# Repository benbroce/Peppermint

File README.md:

# Peppermint
Christmas 2018 &amp; Square Inch Challenge (Hackaday)

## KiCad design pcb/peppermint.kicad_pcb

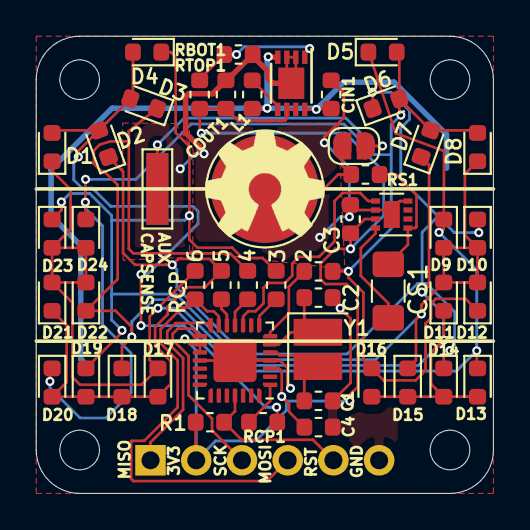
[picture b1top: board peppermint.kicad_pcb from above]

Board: 2 copper layers, 25.4 x 25.4 mm, 55 parts (1 on the bottom side), 27 nets.

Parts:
2, 3, 4, 5, 6: R; R_0603_1608Metric
BT1: CR2032; BatteryHolder_LINX_BAT-HLD-001-SMT_SOLDERPAD
C1, C2: C; C_0603_1608Metric
C3, C4: 0.1uF; C_0603_1608Metric
CIN1: 4.7uF; C_0603_1608Metric
COUT1: 10uF; C_0603_1608Metric
CS1: 22nF; C_1206_3216Metric_Pad1.42x1.75mm_HandSolder
D1, D2, D3, D4, D5, D6, D7, D8, D9, D10, D11, D12, D13, D14, D15, D16, D17, D18, D19, D20, D21, D22, D23, D24: LED; LED_0603_1608Metric
J1: AVR-ISP-6; SIP-6_AVR_ISP
J2: SENSE_ELECTRODE; CapSense_MaskedPad_D6.0mm
J3: SENSE_ELECTRODE_AUX; SMD_WIREPAD_4.0x1.25mm
JP1: Jumper_NO_Small; SolderJumper-2_P1.3mm_Open_RoundedPad1.0x1.5mm
L1: 4.7uH; L_0603_1608Metric
R1: 10K; R_0603_1608Metric
RBOT1: 1M; R_0603_1608Metric
RCP1: R; R_0603_1608Metric
RS1: 10K; R_0603_1608Metric
RTOP1: 1.69M; R_0603_1608Metric
U1: ATmega328P-MMH; QFN-28-1EP_4x4mm_P0.45mm_EP2.4x2.4mm
U2: MCP16251T-I/CH; DFN-8-1EP_3x2mm_P0.5mm_EP1.75x1.45mm
U3: AT42QT1010-MAH; DFN-8-1EP_2x2mm_P0.5mm_EP0.9x1.5mm
Y1: 8MHz; Crystal_SMD_NX3225GD
hole: hole; MountingHole_2.2mm_M2_DIN965
hole#2, hole#3, hole#4: hole; MountingHole_2.2mm_M2_DIN965

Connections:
+3V3: C3.2, C4.2, COUT1.1, J1.2, R1.1, RTOP1.1, U1.3, U1.16, U1.17, U2.6, U2.7, U3.7
CAPSENSE: U1.10, U3.5
CP1: RCP1.2, U1.1
CP2: 2.2, U1.7
CP3: 3.2, U1.8
CP4: 4.2, U1.11
CP5: 5.2, U1.12
CP6: 6.2, J1.4, U1.13
GND: BT1.2, C1.1, C2.2, C3.1, C4.1, CIN1.2, COUT1.2, J1.6, RBOT1.2, U1.4, U1.18, U1.29, U2.2, U2.3, U2.9, U3.4, U3.6, U3.9
MISO: J1.1, U1.14
unnamed: BT1.1, CIN1.1, L1.1, U2.4, U2.8
unnamed: C1.2, U1.5, Y1.2
unnamed: C2.1, U1.6, Y1.1
unnamed: CS1.1, RS1.2, U3.1
unnamed: CS1.2, U3.8
unnamed: 6.1, D1.1, D5.1, D9.1, D13.1, D17.1, D21.2, D22.2, D23.2, D24.2
unnamed: D1.2, D2.2, D3.2, D4.2, RCP1.1
unnamed: 5.1, D2.1, D6.1, D10.1, D14.1, D17.2, D18.2, D19.2, D20.2, D21.1
unnamed: 3.1, D4.1, D8.1, D9.2, D10.2, D11.2, D12.2, D15.1, D19.1, D23.1
unnamed: 4.1, D3.1, D7.1, D11.1, D13.2, D14.2, D15.2, D16.2, D18.1, D22.1
unnamed: 2.1, D5.2, D6.2, D7.2, D8.2, D12.1, D16.1, D20.1, D24.1
unnamed: J2.1, JP1.1, RS1.1
unnamed: J3.1, JP1.2
unnamed: L1.2, U2.5
unnamed: RBOT1.1, RTOP1.2, U2.1
RESET: J1.5, R1.2, U1.25
SCK: J1.3, U1.15

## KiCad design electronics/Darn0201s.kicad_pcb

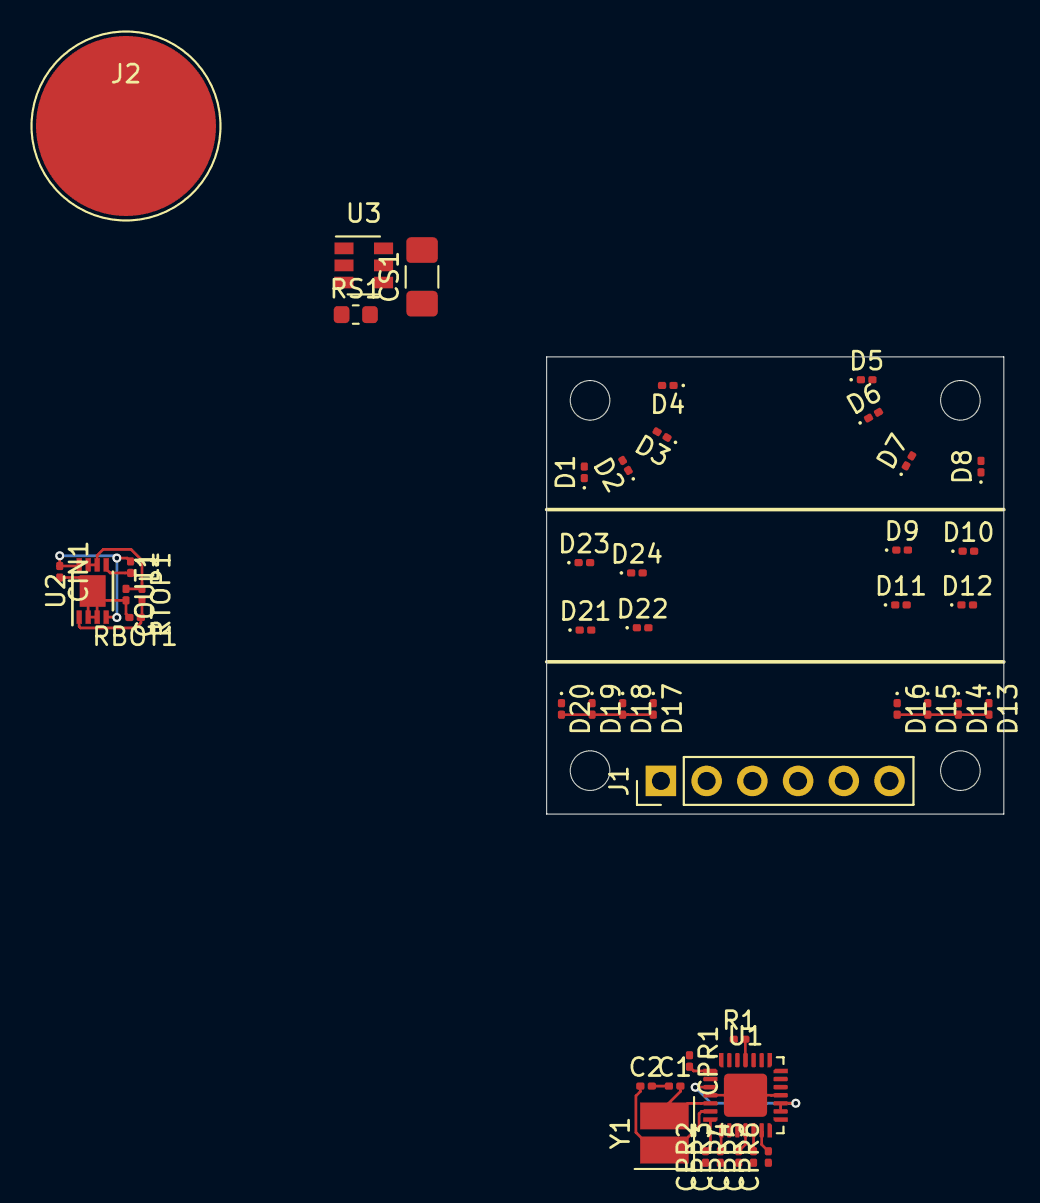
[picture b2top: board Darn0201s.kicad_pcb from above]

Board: 2 copper layers, 25.4 x 25.4 mm, 52 parts (1 on the bottom side), 25 nets.

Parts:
BT1: CR2032; BatteryHolder_LINX_BAT-HLD-001-SMT
C1, C2: C; C_0201_0603Metric
CIN1: 4.7uF; C_0201_0603Metric
COUT1: 10uF; C_0201_0603Metric
CPR1, CPR2, CPR3, CPR4, CPR5, CPR6: R; R_0201_0603Metric
CS1: 22nF; C_1206_3216Metric_Pad1.42x1.75mm_HandSolder
D1, D2, D3, D4, D5, D6, D7, D8, D9, D10, D11, D12, D13, D14, D15, D16, D17, D18, D19, D20, D21, D22, D23, D24: LED; LED_0201_0603Metric
J1: AVR-ISP-6; PinHeader_1x06_P2.54mm_Vertical
J2: SENSE_ELECTRODE; CapSense_MaskedPad_D10.0mm
L1: 4.7uH; L_0201_0603Metric
R1: 10K; R_0201_0603Metric
RBOT1: 1M; R_0201_0603Metric
RS1: 10K; R_0603_1608Metric
RTOP1: 1.69M; R_0201_0603Metric
U1: ATmega328P-MMH; QFN-28-1EP_4x4mm_P0.45mm_EP2.4x2.4mm
U2: MCP16251T-I/CH; DFN-8-1EP_3x2mm_P0.5mm_EP1.75x1.45mm
U3: AT42QT1010-TSHR; SOT-23-6
Y1: 8MHz; Crystal_SMD_NX3225GD
hole: hole; MountingHole_2.2mm_M2_DIN965
hole#2, hole#3, hole#4: hole; MountingHole_2.2mm_M2_DIN965
hole#5: hole; MountingHole_3.2mm_M3_DIN965

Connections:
+3V3: COUT1.1, J1.2, R1.1, RTOP1.1, U1.3, U1.16, U1.17, U2.6, U2.7, U3.5
CAPSENSE: U1.10, U3.1
CP1: CPR1.2, U1.1
CP2: CPR2.2, U1.7
CP3: CPR3.2, U1.8
CP4: CPR4.2, U1.11
CP5: CPR5.2, U1.12
CP6: CPR6.2, J1.4, U1.13
GND: BT1.2, C1.1, C2.2, CIN1.2, COUT1.2, J1.6, RBOT1.2, U1.4, U1.18, U1.29, U2.2, U2.3, U2.9, U3.2, U3.6
MISO: J1.1, U1.14
unnamed: BT1.1, CIN1.1, L1.1, U2.4, U2.8
unnamed: C1.2, U1.5, Y1.2
unnamed: C2.1, U1.6, Y1.1
unnamed: CPR1.1, CPR2.1, D1.2, D2.2, D3.2, D4.2, D5.2, D6.2, D7.2, D8.2, D12.1, D16.1, D20.1, D24.1
unnamed: CPR3.1, D4.1, D8.1, D9.2, D10.2, D11.2, D12.2, D15.1, D19.1, D23.1
unnamed: CPR4.1, D3.1, D7.1, D11.1, D13.2, D14.2, D15.2, D16.2, D18.1, D22.1
unnamed: CPR5.1, D2.1, D6.1, D10.1, D14.1, D17.2, D18.2, D19.2, D20.2, D21.1
unnamed: CPR6.1, D1.1, D5.1, D9.1, D13.1, D17.1, D21.2, D22.2, D23.2, D24.2
unnamed: CS1.1, RS1.2, U3.3
unnamed: CS1.2, U3.4
unnamed: J2.1, RS1.1
unnamed: L1.2, U2.5
unnamed: RBOT1.1, RTOP1.2, U2.1
RESET: J1.5, R1.2, U1.25
SCK: J1.3, U1.15

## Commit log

2018-09-13 Add board sketch
2018-09-17 Create final KiCad schematic & Begin board layout
2018-09-18 Nearly finished board but realized I used 0603 *metric*, not *imperial*. Will change.
2018-09-18 Add reference backup layout for 0201 mistake, Resolve issues, & Finish component layout.
2018-09-20 Finish board routing, Add LED Charlieplexing truth table, Add jumpered electrode just in case
2018-09-21 Finalize PCB, Generate drill files for manufacturing, Begin lasercut enclosure design
2018-09-22 Add gerbers & start BOM
2018-09-25 Refactor & Clean up
2018-10-01 Begin firmware, Remove corrupt BOM, Add txt charlie truth table
2018-10-06 Finish enclosure design (lasercut w/ negative engraving)
2018-10-06 Add code references; Cleanup; Add button interrupt & basic sleep
2018-10-06 Cleanup PCB files, Remove fritzing tests
